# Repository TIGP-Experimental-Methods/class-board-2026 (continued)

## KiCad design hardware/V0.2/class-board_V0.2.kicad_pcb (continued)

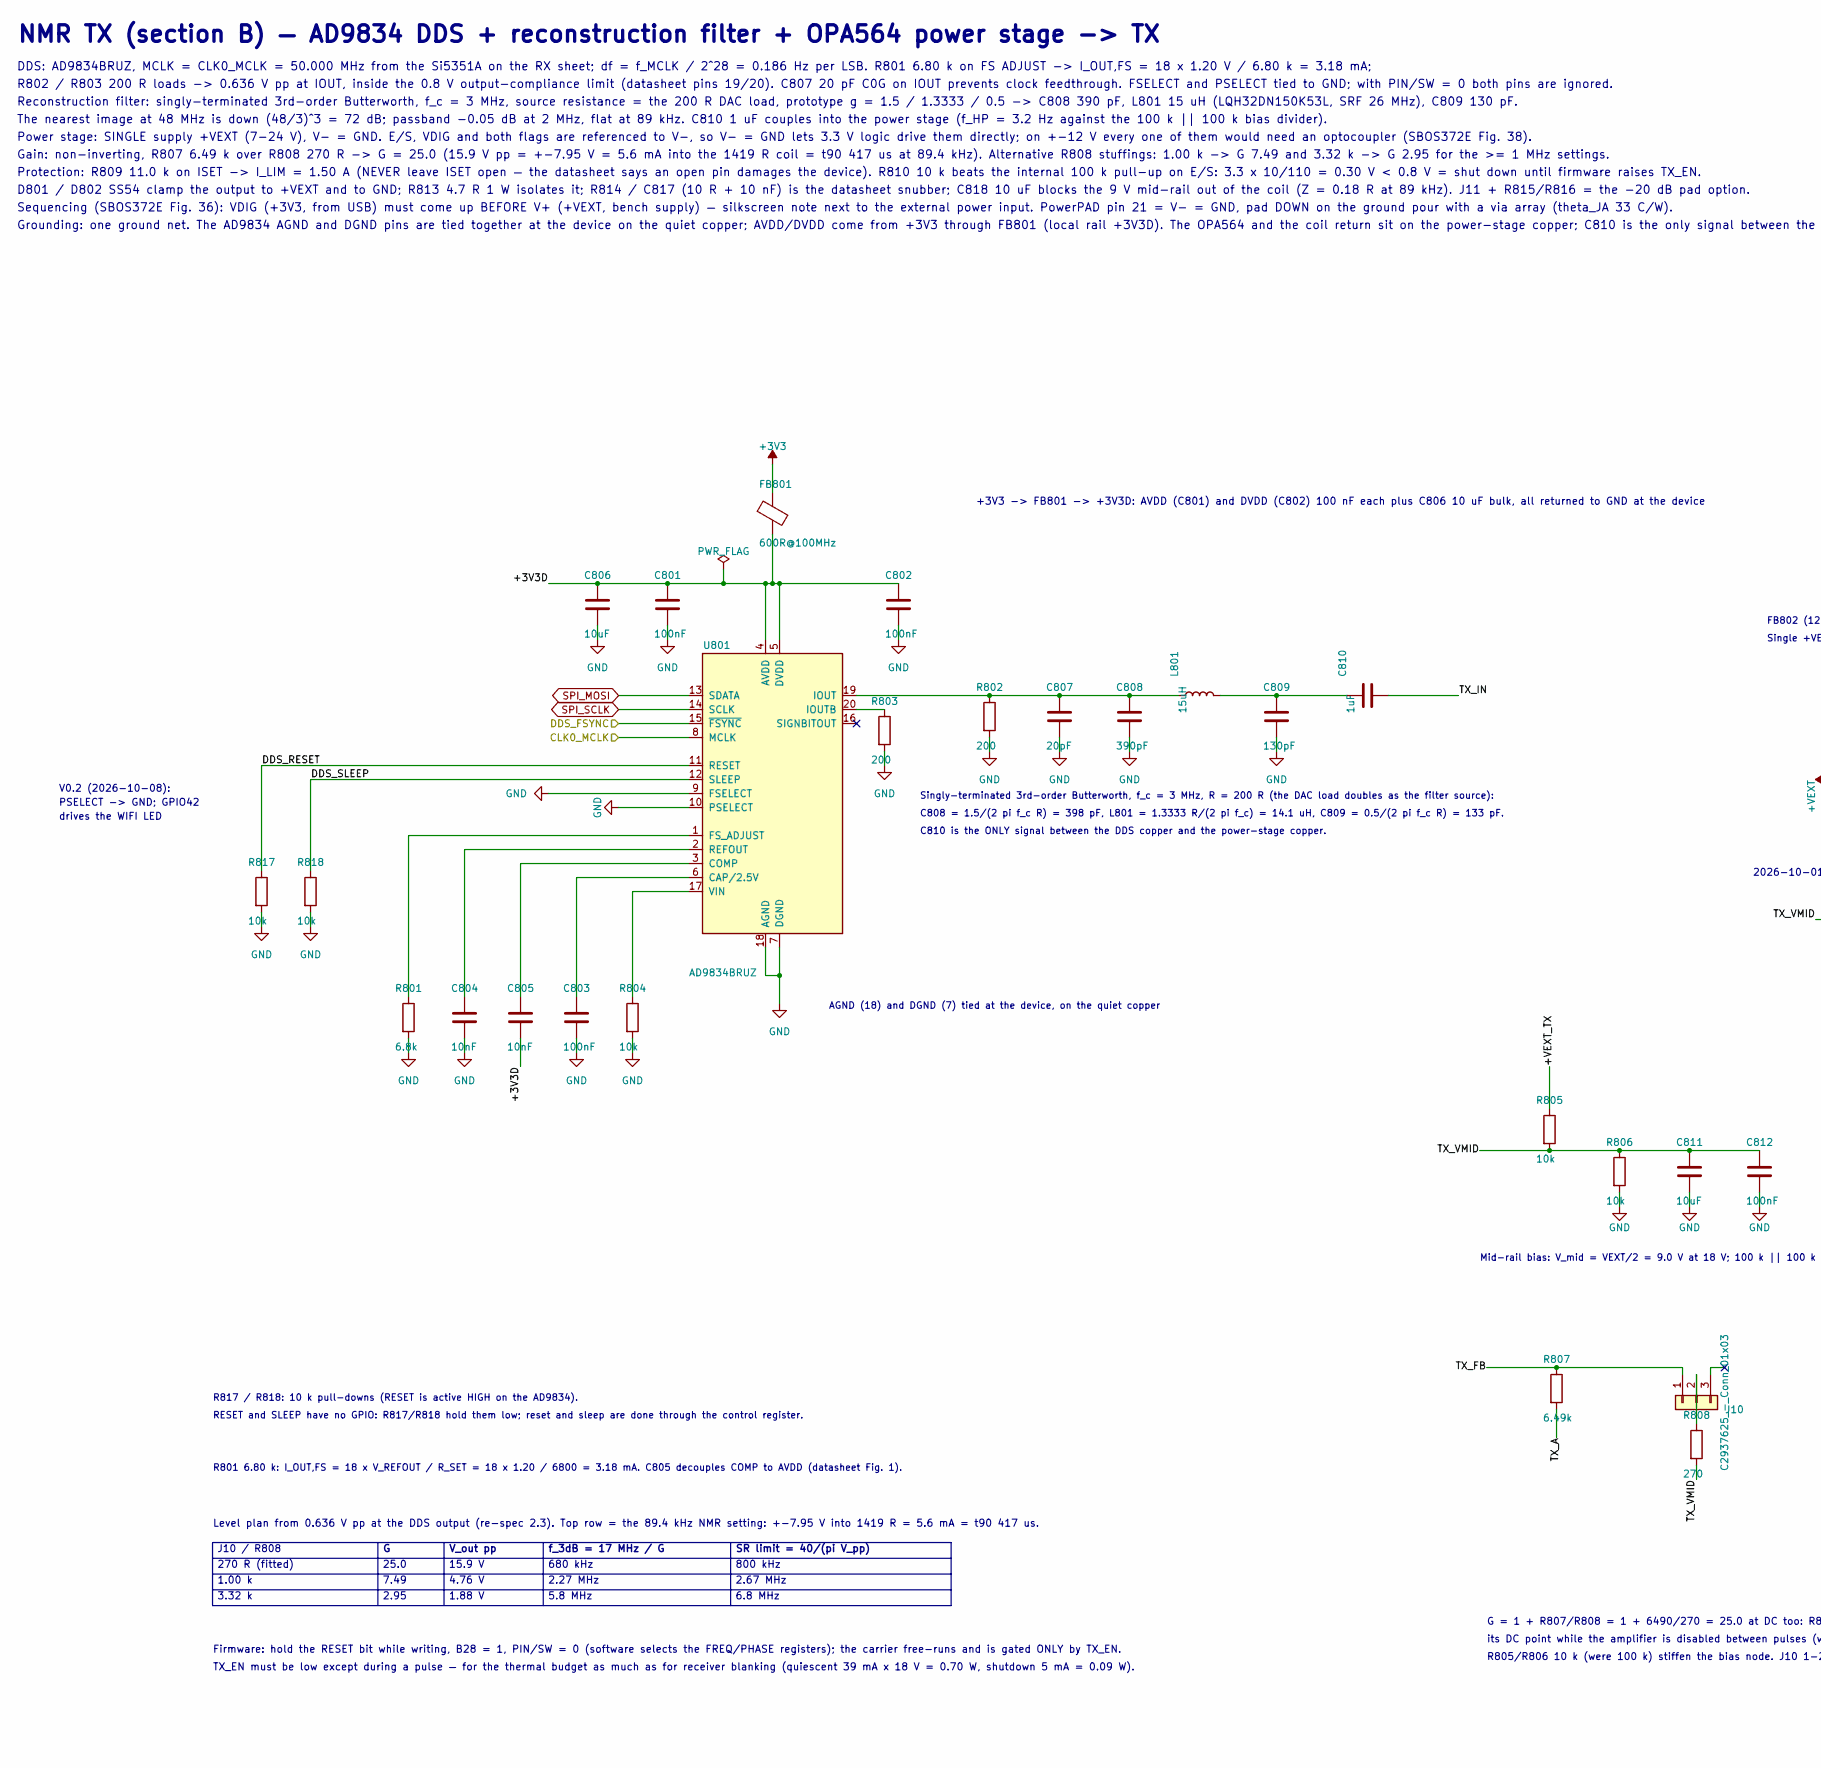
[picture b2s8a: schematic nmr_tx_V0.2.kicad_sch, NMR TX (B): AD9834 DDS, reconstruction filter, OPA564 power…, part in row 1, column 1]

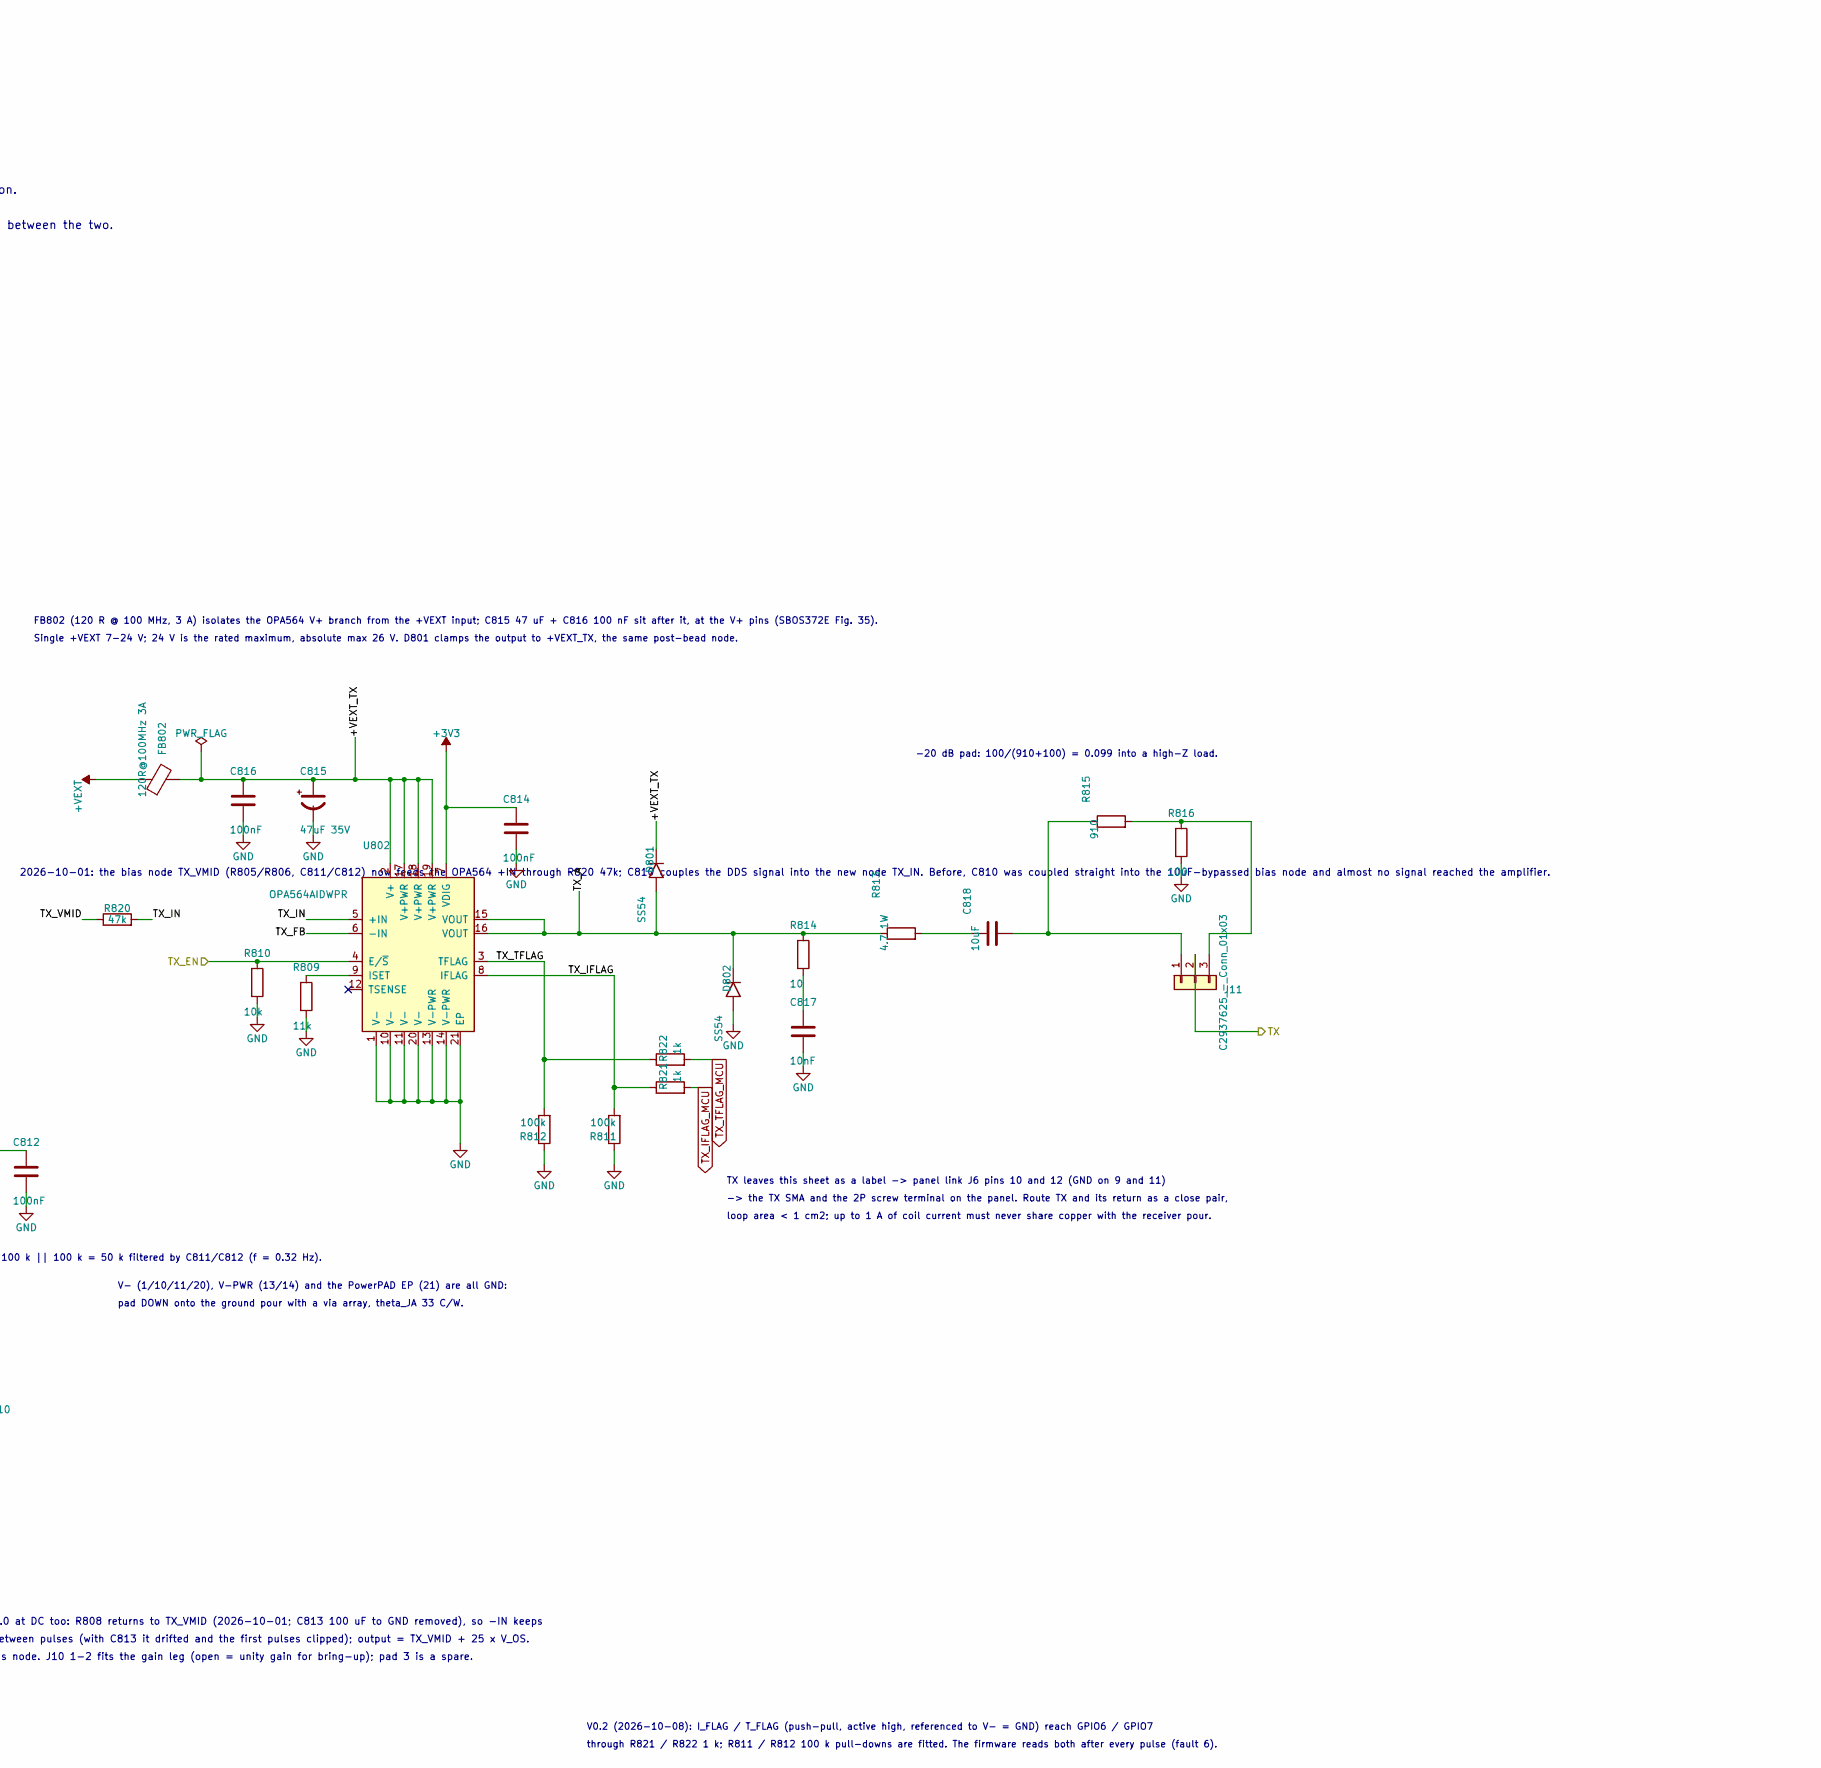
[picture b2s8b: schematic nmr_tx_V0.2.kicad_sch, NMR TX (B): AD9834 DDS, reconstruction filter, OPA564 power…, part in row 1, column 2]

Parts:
C801, C802, C803, C812, C814, C816: 100nF; C_0603_1608Metric; MPN CC0603KRX7R9BB104; LCSC C14663
C804, C805, C817: 10nF; C_0603_1608Metric; MPN CL10B103KB8NNNC; LCSC C1589
C806, C811: 10uF; C_0805_2012Metric; MPN CL21A106KAYNNNE; LCSC C15850
C807: 20pF; C_0603_1608Metric; MPN CL10C200JB8NNNC; LCSC C1648
C808: 390pF; C_0603_1608Metric; MPN CC0603JRNPO9BN391; LCSC C107050
C809: 130pF; C_0603_1608Metric; MPN CC0603JRNPO9BN131; LCSC C519399
C810: 1uF; C_0603_1608Metric; MPN CL10A105KB8NNNC; LCSC C15849
C815: 47uF 35V; CAP-SMD_BD6.3-L6.6-W6.6-FD; MPN HV470M035E055ETR; LCSC C59919
C818: 10uF; C_1206_3216Metric; MPN CL31B106KBHNNNE; LCSC C89632
D801, D802: SS54; SMA_L4.4-W2.8-LS5.4-R-RD; MPN SS54; LCSC C22452
FB801: 600R@100MHz; L0603; MPN GZ1608D601TF; LCSC C1002
FB802: 120R@100MHz 3A; L0603; MPN HCB1608KF-121T30; LCSC C353920
J10, J11: C2937625_-_Conn_01x03; C2937625-HDR-TH_3P-P2.54-V-M; LCSC C2937625
L801: 15uH; IND-SMD_L3.2-W2.5-LQH32CN1R0M53L; MPN LQH32DN150K53L; LCSC C341771
R801: 6.8k; R_0603_1608Metric; MPN 0603WAF6801T5E; LCSC C23212
R802, R803: 200; R_0603_1608Metric; MPN 0603WAF2000T5E; LCSC C8218
R804, R810, R817, R818: 10k; R_0603_1608Metric; MPN 0603WAF1002T5E; LCSC C25804
R805, R806: 10k; R_0603_1608Metric; MPN 0603WAF1003T5E; LCSC C25804
R807: 6.49k; R_0603_1608Metric; MPN 0603WAF6491T5E; LCSC C23088
R808: 270; R_0603_1608Metric; MPN 0603WAF2700T5E; LCSC C22966
R809: 11k; R_0603_1608Metric; MPN 0603WAF1102T5E; LCSC C25950
R811, R812: 100k; R_0603_1608Metric; MPN 0603WAF1003T5E; JLC_CLASS Basic
R813: 4.7 1W; R_2512_6332Metric; MPN FRC2512F4R70TS; LCSC C2999606
R814: 10; R_0805_2012Metric; MPN 0805W8F100JT5E; LCSC C17415
R815: 910; R_0603_1608Metric; MPN 0603WAF9100T5E; LCSC C23264
R816: 100; R_0603_1608Metric; MPN 0603WAF1000T5E; LCSC C22775
R820: 47k; R_0603_1608Metric; LCSC C25819
R821, R822: 1k; R_0603_1608Metric; MPN 0603WAF1001T5E; JLC_CLASS Basic
U801: AD9834BRUZ; TSSOP-20_L6.5-W4.4-P0.65-LS6.4-BL; MPN AD9834BRUZ; LCSC C116589
U802: OPA564AIDWPR; HSOP-20_L12.9-W7.5-P1.27-BL-EP-A; MPN OPA564AIDWPR; LCSC C188648

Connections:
+3V3: C814.1, FB801.1, U802.7 (VDIG); also elsewhere on the board
/b1_inputs/TX: J11.2; also elsewhere on the board
/base_mcu/DDS_FSYNC: U801.15 (~FSYNC); also elsewhere on the board
/base_mcu/TX_EN: R810.1, U802.4 (E/~S); also elsewhere on the board
/nmr_rx/CLK0_MCLK: U801.8 (MCLK); also elsewhere on the board
/nmr_tx/DDS_RESET: R817.1, U801.11 (RESET)
/nmr_tx/DDS_SLEEP: R818.1, U801.12 (SLEEP)
/nmr_tx/TX_A: D801.1 (A), D802.2 (K), R807.2, R813.1, R814.1, U802.15 (VOUT), U802.16 (VOUT)
/nmr_tx/TX_FB: J10.1, R807.1, U802.6 (-IN)
/nmr_tx/TX_IFLAG: R811.2, R821.1, U802.8 (IFLAG)
/nmr_tx/TX_IN: C810.2, R820.2, U802.5 (+IN)
/nmr_tx/TX_TFLAG: R812.2, R822.1, U802.3 (TFLAG)
/nmr_tx/TX_VMID: C811.1, C812.1, R805.2, R806.1, R808.2, R820.1
GND: C801.2, C802.2, C803.2, C804.2, C806.2, C807.2, C808.2, C809.2, C811.2, C812.2, C814.2, C815.2, C816.2, C817.2, D802.1 (A), R801.2, R802.2, R803.2, R804.2, R806.2, R809.2, R810.2, R811.1, R812.1, R816.2, R817.2, R818.2, U801.7 (DGND), U801.9 (FSELECT), U801.10 (PSELECT), U801.18 (AGND), U802.1 (V-), U802.10 (V-), U802.11 (V-), U802.13 (V-PWR), U802.14 (V-PWR), U802.20 (V-), U802.21 (EP); also elsewhere on the board
unnamed: C809.1, C810.1, L801.2
unnamed: C817.1, R814.2
unnamed: C818.1, R813.2
unnamed: J10.2, R808.1
unnamed: C818.2, J11.1, R815.1
unnamed: J11.3, R815.2, R816.1
unnamed: C803.1, U801.6 (CAP/2.5V)
unnamed: C805.1, U801.3 (COMP)
unnamed: R801.1, U801.1 (FS_ADJUST)
unnamed: C807.1, C808.1, L801.1, R802.1, U801.19 (IOUT)
unnamed: R803.1, U801.20 (IOUTB)
unnamed: C804.1, U801.2 (REFOUT)
unnamed: R804.1, U801.17 (VIN)
unnamed: R809.1, U802.9 (ISET)
SPI_MOSI: U801.13 (SDATA); also elsewhere on the board
SPI_SCLK: U801.14 (SCLK); also elsewhere on the board
TX_IFLAG_MCU: R821.2; also elsewhere on the board
TX_TFLAG_MCU: R822.2; also elsewhere on the board

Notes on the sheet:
Protection: R809 11.0 k on ISET -> I_LIM = 1.50 A (NEVER leave ISET open — the datasheet says an open pin damages the device). R810 10 k beats the internal 100 k pull-up on E/S: 3.3 x 10/110 = 0.30 V < 0.8 V = shut down until firmware raises TX_EN.
its DC point while the amplifier is disabled between pulses (with C813 it drifted and the first pulses clipped); output = TX_VMID + 25 x V_OS.
3.32 k
J10 / R808
R805/R806 10 k (were 100 k) stiffen the bias node. J10 1-2 fits the gain leg (open = unity gain for bring-up); pad 3 is a spare.
6.8 MHz
2.95
V_out pp
7.49
800 kHz
NMR TX (section B) — AD9834 DDS + reconstruction filter + OPA564 power stage -> TX
loop area < 1 cm2; up to 1 A of coil current must never share copper with the receiver pour.
Level plan from 0.636 V pp at the DDS output (re-spec 2.3). Top row = the 89.4 kHz NMR setting: +-7.95 V into 1419 R = 5.6 mA = t90 417 us.
FB802 (120 R @ 100 MHz, 3 A) isolates the OPA564 V+ branch from the +VEXT input; C815 47 uF + C816 100 nF sit after it, at the V+ pins (SBOS372E Fig. 35).
1.88 V
TX_EN must be low except during a pulse — for the thermal budget as much as for receiver blanking (quiescent 39 mA x 18 V = 0.70 W, shutdown 5 mA = 0.09 W).
G = 1 + R807/R808 = 1 + 6490/270 = 25.0 at DC too: R808 returns to TX_VMID (2026-10-01; C813 100 uF to GND removed), so -IN keeps
Singly-terminated 3rd-order Butterworth, f_c = 3 MHz, R = 200 R (the DAC load doubles as the filter source):
15.9 V
Gain: non-inverting, R807 6.49 k over R808 270 R -> G = 25.0 (15.9 V pp = +-7.95 V = 5.6 mA into the 1419 R coil = t90 417 us at 89.4 kHz). Alternative R808 stuffings: 1.00 k -> G 7.49 and 3.32 k -> G 2.95 for the >= 1 MHz settings.
4.76 V
Sequencing (SBOS372E Fig. 36): VDIG (+3V3, from USB) must come up BEFORE V+ (+VEXT, bench supply) — silkscreen note next to the external power input. PowerPAD pin 21 = V- = GND, pad DOWN on the ground pour with a via array (theta_JA 33 C/W).
5.8 MHz
C808 = 1.5/(2 pi f_c R) = 398 pF, L801 = 1.3333 R/(2 pi f_c) = 14.1 uH, C809 = 0.5/(2 pi f_c R) = 133 pF.
2.27 MHz
f_3dB = 17 MHz / G
270 R (fitted)
Mid-rail bias: V_mid = VEXT/2 = 9.0 V at 18 V; 100 k || 100 k = 50 k filtered by C811/C812 (f = 0.32 Hz).
SR limit = 40/(pi V_pp)
R817 / R818: 10 k pull-downs (RESET is active HIGH on the AD9834).
-20 dB pad: 100/(910+100) = 0.099 into a high-Z load.
DDS: AD9834BRUZ, MCLK = CLK0_MCLK = 50.000 MHz from the Si5351A on the RX sheet; df = f_MCLK / 2^28 = 0.186 Hz per LSB. R801 6.80 k on FS ADJUST -> I_OUT,FS = 18 x 1.20 V / 6.80 k = 3.18 mA;
The nearest image at 48 MHz is down (48/3)^3 = 72 dB; passband -0.05 dB at 2 MHz, flat at 89 kHz. C810 1 uF couples into the power stage (f_HP = 3.2 Hz against the 100 k || 100 k bias divider).
2.67 MHz
pad DOWN onto the ground pour with a via array, theta_JA 33 C/W.
R801 6.80 k: I_OUT,FS = 18 x V_REFOUT / R_SET = 18 x 1.20 / 6800 = 3.18 mA. C805 decouples COMP to AVDD (datasheet Fig. 1).
1.00 k
-> the TX SMA and the 2P screw terminal on the panel. Route TX and its return as a close pair,
V- (1/10/11/20), V-PWR (13/14) and the PowerPAD EP (21) are all GND:
Reconstruction filter: singly-terminated 3rd-order Butterworth, f_c = 3 MHz, source resistance = the 200 R DAC load, prototype g = 1.5 / 1.3333 / 0.5 -> C808 390 pF, L801 15 uH (LQH32DN150K53L, SRF 26 MHz), C809 130 pF.

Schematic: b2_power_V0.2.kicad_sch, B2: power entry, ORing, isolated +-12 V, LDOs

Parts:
C201, C206, C207, C214: 22uF; C_1206_3216Metric; MPN CL31A226KAHNNNE; LCSC C12891
C202, C208, C209, C212, C215: 100nF; C_0603_1608Metric; MPN CC0603KRX7R9BB104; LCSC C14663
C203, C204, C211, C213, C216, C217: 10uF; C_0805_2012Metric; MPN CL21A106KAYNNNE; LCSC C15850
C210: 1uF; C_0603_1608Metric; MPN CL10A105KB8NNNC; LCSC C15849
D201, D202: SMF5.0A; SOD-123FL_L2.7-W1.8-LS3.8-RD; MPN SMF5.0A; LCSC C19077497
D203, D204, D205, D206: GREEN; LED0805-R-RD; MPN KT-0805G; LCSC C2297
F201, F202: 1.5A polyfuse; F1812; MPN 1812L150/33GR; LCSC C18198333
FB201, FB202, FB203, FB204: 600R@100MHz; L0603; MPN GZ1608D601TF; LCSC C1002
J201: USB-C 16P; USB-C-SMD_TYPE-C-16PIN-2MD-073; MPN TYPE-C 16PIN 2MD(073); LCSC C2765186
J202: DC005-T20; DC-IN-TH_DC005-T20; MPN DC005-T20; LCSC C111567
PS201, PS202: B0512S-2WR3; PWRM-TH_IBXX05S-2WR3; MPN B0512S-2WR3; LCSC C5369475
R201, R202: 5.1k; R_0603_1608Metric; MPN 0603WAF5101T5E; LCSC C23186
R203, R204, R205, R206, R207, R208: 2.2k; R_0603_1608Metric; MPN 0603WAF2201T5E; LCSC C4190
R209, R210: 1k; R_0603_1608Metric; MPN 0603WAF1001T5E; LCSC C21190
R211, R212: 4.7k; R_0603_1608Metric; MPN 0603WAF4701T5E; LCSC C23162
TP201: 5V_RAW; TestPoint_Pad_D1.5mm
TP202: +3V3; TestPoint_Pad_D1.5mm
TP203: +12V; TestPoint_Pad_D1.5mm
TP204: -12V; TestPoint_Pad_D1.5mm
TP205: +5VA; TestPoint_Pad_D1.5mm
U201, U202: LM66100DCKR; SC-70-6_L2.0-W1.3-P0.65-LS2.1-BL; MPN LM66100DCKR; LCSC C2869734
U203: 78L05G-AB3-R; SOT-89-3_L4.5-W2.5-P1.50-LS4.2-BR; MPN 78L05G-AB3-R; LCSC C71136
U204: AMS1117-3.3; SOT-223-3_L6.5-W3.4-P2.30-LS7.0-BR; MPN AMS1117-3.3; LCSC C6186

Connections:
+3V3: C214.1, C215.1, R210.1, TP202.1 (1_1), U204.2 (VOUT); also elsewhere on the board
+5VA: C211.1, C212.1, TP205.1 (1_1), U203.1 (OUT); also elsewhere on the board
/b2_power/USB_D_N: J201.A7 (D-), J201.B7 (D-); also elsewhere on the board
/b2_power/USB_D_P: J201.A6 (D+), J201.B6 (D+); also elsewhere on the board
GND: C201.2, C202.2, C203.2, C204.2, C206.2, C207.2, C208.2, C209.2, C210.2, C211.2, C212.2, C213.2, C214.2, C215.2, C216.2, C217.2, D201.2 (A), D202.2 (A), D203.2 (A), D204.2 (A), D205.2 (A), D206.1 (K), J201.13 (SHIELD), J201.14 (SHIELD), J201.A1B12 (GND), J201.B1A12 (GND), J202.2 (SLEEVE), PS201.2 (-VIN), PS201.4 (-VO), PS202.2 (-VIN), PS202.6 (+VO), R201.2, R202.2, R203.2, R204.2, R205.2, R206.2, R207.2, R208.2, U201.2 (GND), U201.5 (~ST), U202.2 (GND), U202.5 (~ST), U203.2 (GND), U204.1 (GND); also elsewhere on the board
unnamed: D203.1 (K), R209.2
unnamed: D204.1 (K), R210.2
unnamed: D205.1 (K), R211.2
unnamed: D206.2 (A), R212.2
unnamed: F201.1, J201.A4B9 (VBUS), J201.B4A9 (VBUS)
unnamed: J201.A5 (CC1), R201.1
unnamed: J201.B5 (CC2), R202.1
unnamed: F202.1, J202.1 (TIP)
unnamed: FB203.1, PS201.6 (+VO)
unnamed: FB204.1, PS202.4 (-VO)

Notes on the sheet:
Isolated 2 W modules: input 4.5-5.5 V, 454 mA full load, ripple 80 mVp-p max, Cout <= 560 uF, 1.5 kVDC isolation (YLPTEC datasheet)
CC1/CC2 5.1k = UFP sink, 5 V. Shield pads to GND directly (no chassis).
+5V_RAW rail (both LM66100 outputs): bulk 22 uF + 100 nF, green LED (2.9 mA); PWR_FLAG = ideal diodes drive the rail
+3V3: AMS1117-3.3 (SOT-223), 22 uF ceramic out (tantalum 3216 drop-in if needed), pin 4 = tab (same VOUT net on the footprint)
+-12 V: two unregulated B0512S-2WR3 (10 % minimum load rule!): +12 V rail loaded by 78L05 + bleeder, -12 V rail by OPA2192 + 3 x 2.2k bleeder (16 mA) so both stay inside the +-15 % envelope (datasheet p.3/4).
+12V: FB + 22 uF + 100 nF at the module; 3 x 2.2k = 16 mA bleeder guarantees the 10 % minimum load with 78L05 load included
B2 — POWER: USB-C / 5 V jack entry, ideal-diode ORing, +-12 V isolated modules, +5VA and +3V3 LDOs
78L05G (SOT-89, 350 mW max): +12 V -> +5VA for ADS8688/DAC8563 AVDD; ~17 mA -> 0.12 W. AMS1117-3.3: 22 uF output required for stability (datasheet 'Stability'); ceramic used, tantalum drop-in (3216) if the rail rings.
Jack: 5 V DC, centre +, 5.5/2.1 mm, 1.5-3 A. Switch pin unused.
Rail test points
Entry: 1.5 A polyfuse -> SMF5.0A TVS -> LM66100 ideal diode per input, CE (pin 3) tied to the device's own VOUT (datasheet SLVSEZ8A 8.3.2, always-on reverse-current blocking): the two inputs diode-OR, the higher source wins, no back-feed. Drop ~0.18 V typ at 1.2 A.
All power-module outputs are referenced to GND (-12 V module: +Vo = GND). The board has one ground net; the analog/digital split is in the layout only.
-12V: module #2 with +Vo on GND; FB in the -Vo line; 3 x 2.2k bleeder (16 mA) + LED keep the 10 % minimum load
+5VA: 78L05G from +12V (dropout 1.7 V), ADC/DAC analog supply; 0.12 W at 17 mA
V0.2 (2026-10-08): CE -> VOUT (was GND)

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
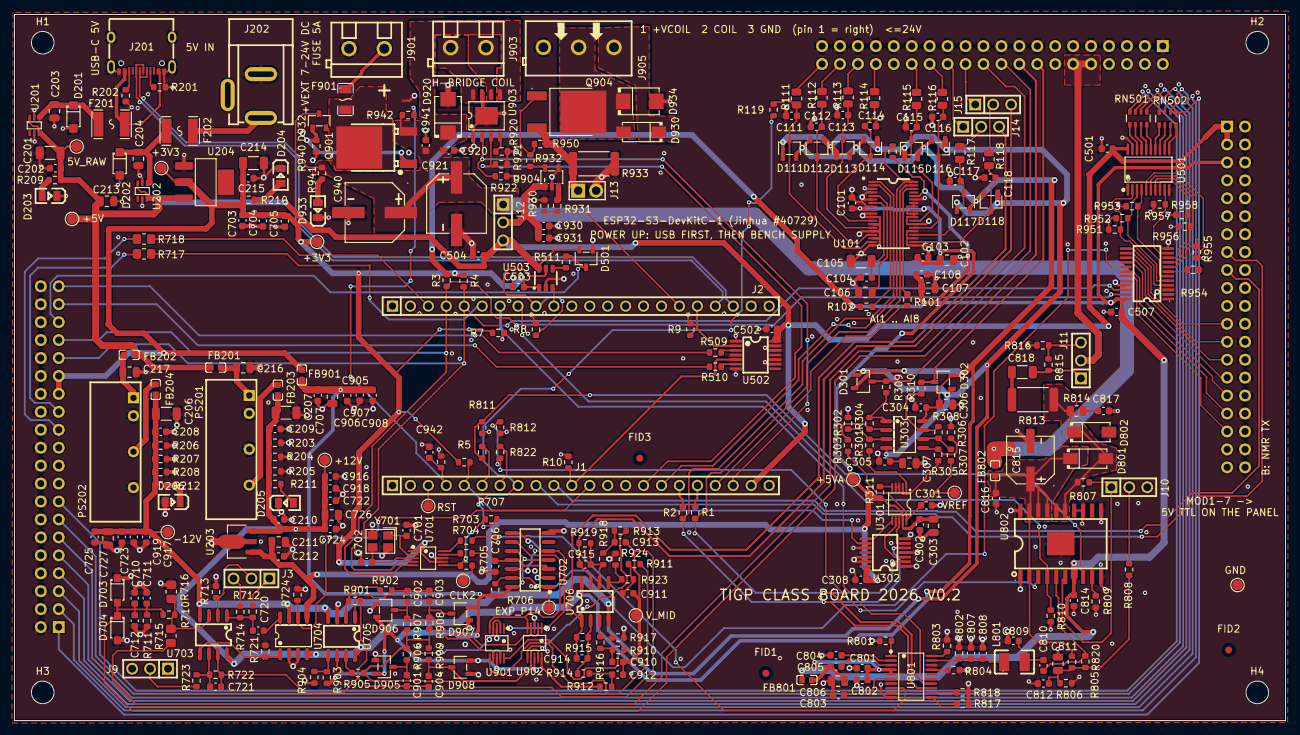
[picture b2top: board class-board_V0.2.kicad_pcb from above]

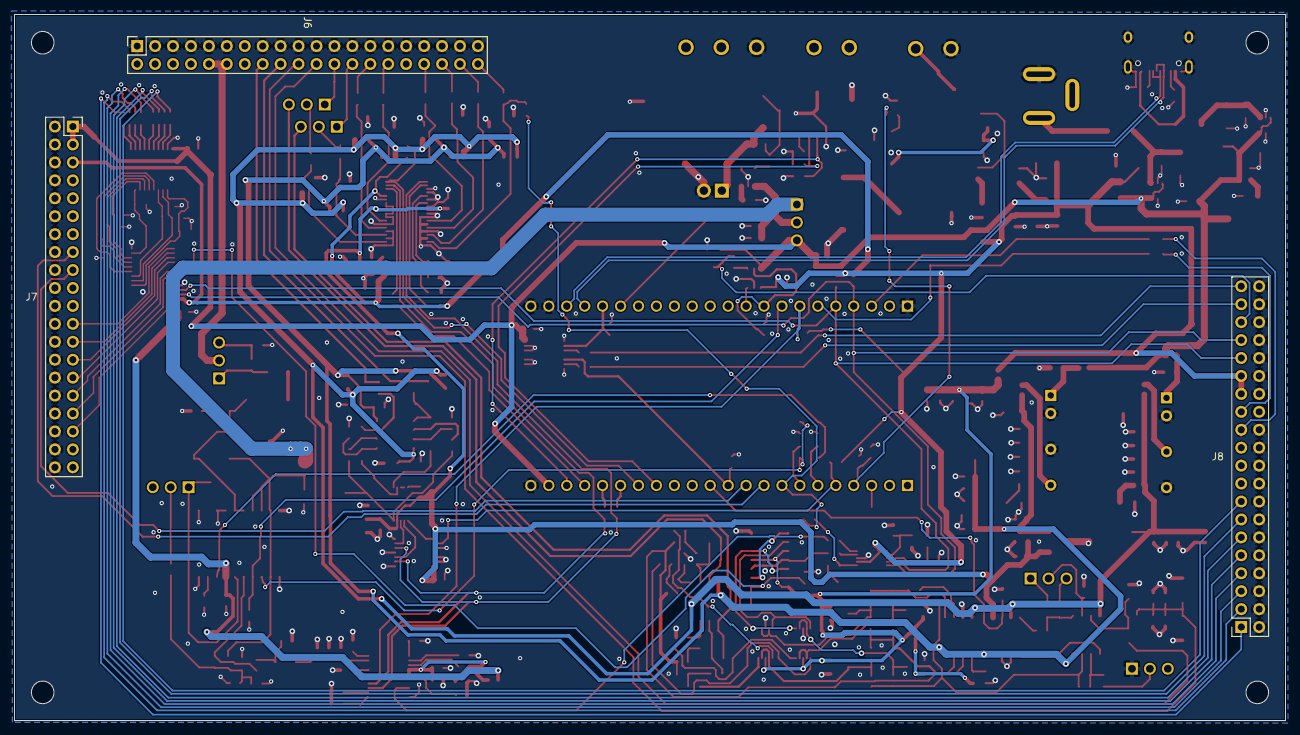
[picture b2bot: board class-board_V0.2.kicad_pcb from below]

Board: 4 copper layers, 180.0 x 100.0 mm, 342 parts (3 on the bottom side), 214 nets.

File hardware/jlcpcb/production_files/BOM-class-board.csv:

Comment,Designator,Footprint,LCSC,Quantity
600R@100MHz,"FB201,FB202,FB203,FB204,FB801,FB901",L0603,C1002,6
390pF,C808,C_0603_1608Metric,C107050,1
OPA2192IDR,U303,SOIC-8_L4.9-W3.9-P1.27-LS6.0-BL,C110074,1
1.00k,"R714,R723,R910,R911,R912,R913,R914,R916,R918,R923",R_0603_1608Metric,C110776,10
TS5A23157DGSR,"U901,U902",MSOP-10_L3.0-W3.0-P0.50-LS5.0-BL,C11133,2
DC005-T20,J202,DC-IN-TH_DC005-T20,C111567,1
BZX84C12,D932,SOT-23-3_L2.9-W1.3-P1.90-LS2.4-BR,C112551,1
AD9834BRUZ,U801,TSSOP-20_L6.5-W4.4-P0.65-LS6.4-BL,C116589,1
SMBJ26A,"D920,D931",SMB_L4.6-W3.6-LS5.3-RD,C123820,2
40.2k,"R302,R304,R306,R308",R_0603_1608Metric,C12447,4
22uF,"C105,C201,C206,C207,C214",C_1206_3216Metric,C12891,5
74HCT125PW,"U302,U502",TSSOP-14_L5.0-W4.4-P0.65-LS6.4-BL,C131316,2
100nF,"C108,C202,C208,C209,C212,C215,C302,C304,C305,C308,C501,C502,C503,C504,C507,C703,C705,C707,C722,C723,C724,C725,C801,C802,C803,C812,C814,C816,C906,C907,C908,C916,C917,C918,C919,C920,C931,C941",C_0603_1608Metric,C14663,38
100pF,"C711,C721",C_0603_1608Metric,C14858,2
DAC8563SDGSR,U301,VSSOP-10_L3.0-W3.0-P0.50-LS4.9-BL,C1554729,1
1uF,"C101,C103,C104,C210,C301,C704,C810,C930",C_0603_1608Metric,C15849,8
10uF,"C102,C106,C107,C203,C204,C211,C213,C216,C217,C303,C306,C307,C726,C727,C806,C811,C905",C_0805_2012Metric,C15850,17
1nF,"C111,C112,C113,C114,C115,C116,C117,C118",C_0603_1608Metric,C1588,8
10nF,"C720,C804,C805,C817,C901,C902,C903,C904,C910,C911,C912,C913",C_0603_1608Metric,C1589,12
20pF,C807,C_0603_1608Metric,C1648,1
22pF,C712,C_0603_1608Metric,C1653,1
47pF,C706,C_0603_1608Metric,C1671,1
10,R814,R_0805_2012Metric,C17415,1
0,"R717,R718",R_0805_2012Metric_Pad1.20x1.40mm_HandSolder,C17477,2
1.5A polyfuse,"F201,F202",F1812,C18198333,2
OPA1656IDR,U703,SOIC-8_L5.0-W4.0-P1.27-LS6.0-BL,C1849431,1
OPA564AIDWPR,U802,HSOP-20_L12.9-W7.5-P1.27-BL-EP-A,C188648,1
SMF5.0A,"D201,D202",SOD-123FL_L2.7-W1.8-LS3.8-RD,C19077497,2
1k,"RN501,RN502",R_Array_Convex_4x0603,C20197,2
UCC27517DBVR,U904,SOT-23-5_L3.0-W1.7-P0.95-LS2.8-BR,C20623191,1
1k,"R111,R112,R113,R114,R115,R116,R117,R118,R209,R210",R_0603_1608Metric,C21190,10
TCA9535PWR,U505,TSSOP-24_L7.8-W4.4-P0.65-LS6.4-BL,C22396388,1
SS54,"D801,D802,D930",SMA_L4.4-W2.8-LS5.4-R-RD,C22452,3
100,"R704,R710,R713,R816,R905,R931",R_0603_1608Metric,C22775,6
10,R932,R_0603_1608Metric,C22859,1
1M,R711,R_0603_1608Metric,C22935,1
270,R808,R_0603_1608Metric,C22966,1
GREEN,"D203,D204,D205,D206,D933",LED0805-R-RD,C2297,5
6.49k,R807,R_0603_1608Metric,C23088,1
33,"R1,R101,R2,R511,R703,R705",R_0603_1608Metric,C23140,6
4.7k,"R211,R212,R3,R4,R941",R_0603_1608Metric,C23162,5
49.9,"R309,R310,R509,R510",R_0603_1608Metric,C23185,4
5.1k,"R201,R202",R_0603_1608Metric,C23186,2
6.8k,R801,R_0603_1608Metric,C23212,1
9.1k,R722,R_0603_1608Metric,C23260,1
910,R815,R_0603_1608Metric,C23264,1
BAV99,"D111,D112,D113,D114,D115,D116,D117,D118,D301,D302,D501,D905,D906,D907,D908",SOT-23-3_L2.9-W1.6-P1.90-LS2.8-BR,C2500,15
10k,"R102,R301,R303,R305,R307,R311,R706,R721,R724,R804,R805,R806,R810,R817,R818,R903,R904,R906,R907,R908,R909,R921,R922,R930,R950,R951,R952,R953,R954,R955,R956,R957,R958",R_0603_1608Metric,C25804,33
47k,"R820,R940",R_0603_1608Metric,C25819,2
11k,R809,R_0603_1608Metric,C25950,1
"74HC74D,653",U702,SOIC-14_L8.7-W3.9-P1.27-LS6.0-BL,C27597,1
USB-C 16P,J201,USB-C-SMD_TYPE-C-16PIN-2MD-073,C2765186,1
LM66100DCKR,"U201,U202",SC-70-6_L2.0-W1.3-P0.65-LS2.1-BL,C2869734,2
0R,R933,R_2512_6332Metric,C2889851,1
C2937625_-_Conn_01x03,"J10,J11,J12,J14,J15,J3,J9",C2937625-HDR-TH_3P-P2.54-V-M,C2937625,7
4.7 1W,R813,R_2512_6332Metric,C2999606,1
15uH,L801,IND-SMD_L3.2-W2.5-LQH32CN1R0M53L,C341771,1
120R@100MHz 3A,FB802,L0603,C353920,1
100uF 35V,"C921,C940",CAP-SMD_BD8.0-L8.3-W8.3-LS9.3-FD,C37309,2
AOD4185,Q901,TO-252-3_L6.6-W6.1-P4.57-LS9.9-BR-CW,C400894,1
2.2k,"R203,R204,R205,R206,R207,R208",R_0603_1608Metric,C4190,6
KF301-5.0-2P,"J901,J903",CONN-TH_P5.00_KF301-5.0-2P,C474881,2
KF301-5.0-3P,J905,CONN-TH_3P-P5.00_KF301-5.0-3P,C474882,1
SI5351A-B-GT,U701,MSOP-10_L3.0-W3.0-P0.50-LS5.0-BL,C504891,1
SN74AHCT541PWR,U501,TSSOP-20_L6.5-W4.4-P0.65-LS6.4-BL,C50989,1
Panel link 2x20 female,"J6,J7,J8",PinSocket_2x20_P2.54mm_Vertical,C5124634,3
560pF,"C914,C915",C_0603_1608Metric,C513644,2
3.9pF,"C701,C702",C_0603_1608Metric,C519107,2
130pF,C809,C_0603_1608Metric,C519399,1
ADS8688IDBTR,U101,TSSOP-38_L9.7-W4.4-P0.50-LS6.4-BL,C527390,1
B0512S-2WR3,"PS201,PS202",PWRM-TH_IBXX05S-2WR3,C5369475,2
5A fast,F901,F1206,C57525,1
1.2nF,C710,C_0603_1608Metric,C576816,1
47uF 35V,C815,CAP-SMD_BD6.3-L6.6-W6.6-FD,C59919,1
AMS1117-3.3,U204,SOT-223-3_L6.5-W3.4-P2.30-LS7.0-BR,C6186,1
DG419DY-T1-E3,U704,SOIC-8_L4.9-W3.9-P1.27-LS6.0-BL,C6581,1
78L05G-AB3-R,U203,SOT-89-3_L4.5-W2.5-P1.50-LS4.2-BR,C71136,1
20.0k,"R915,R917,R919,R924",R_0603_1608Metric,C723637,4
DevKit J1 (left row),"J1,J2",HDR-TH_22P-P2.54-V-F,C7499337,2
DRV8871DDAR,U903,SO-8_L4.9-W3.9-P1.27-LS6.0-BL-EP,C75864,1
SN74LVC1T45DBVR,U503,SOT-23-6_L2.9-W1.6-P0.95-LS2.8-BR,C7843,1
1N4148W,"D703,D704",SOD-123F_L2.7-W1.6-LS3.8-RD,C81598,2
200,"R802,R803",R_0603_1608Metric,C8218,2
32k,R920,R_0603_1608Metric,C861325,1
10uF,C818,C_1206_3216Metric,C89632,1
25 MHz,Y701,CRYSTAL-SMD_4P-L3.2-W2.5-BL,C9006,1
OPA1612AIDR,"U705,U706",SOIC-8_L5.0-W4.0-P1.27-LS6.0-BL,C94590,2
10.0k,"R712,R901,R902",R_0603_1608Metric,C95204,3
AOD4184A,Q904,TO-252-2_L6.6-W6.1-P4.57-LS9.9-TL-CW,C99124,1
